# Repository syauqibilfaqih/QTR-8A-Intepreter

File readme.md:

# QTR-8A Interpreter 

This is the repository of QTR-8A Interpreter circuit that supports both digital data transmission through gpio pins and UART communication between master microcontroller and slave microcontroller, which is Arduino Nano, to read the QTR-8A sensor data. Use KiCad to open the schematic and board file, whereas use PlatformIO VS Code to open the code and build it.

To calibrate the line sensor, there are three ways to trigger the calibration mode:

1. By pressing button
2. By sending command "clib" via UART
3. By giving active signal to pin 12

Once the calibration mode is activated, move the sensors to get the black and white surface of the track. When it's done, the led indicators will show the correct reading state, where if the sensor read the black surface, the led will be turned on, otherwise it will be turned off.

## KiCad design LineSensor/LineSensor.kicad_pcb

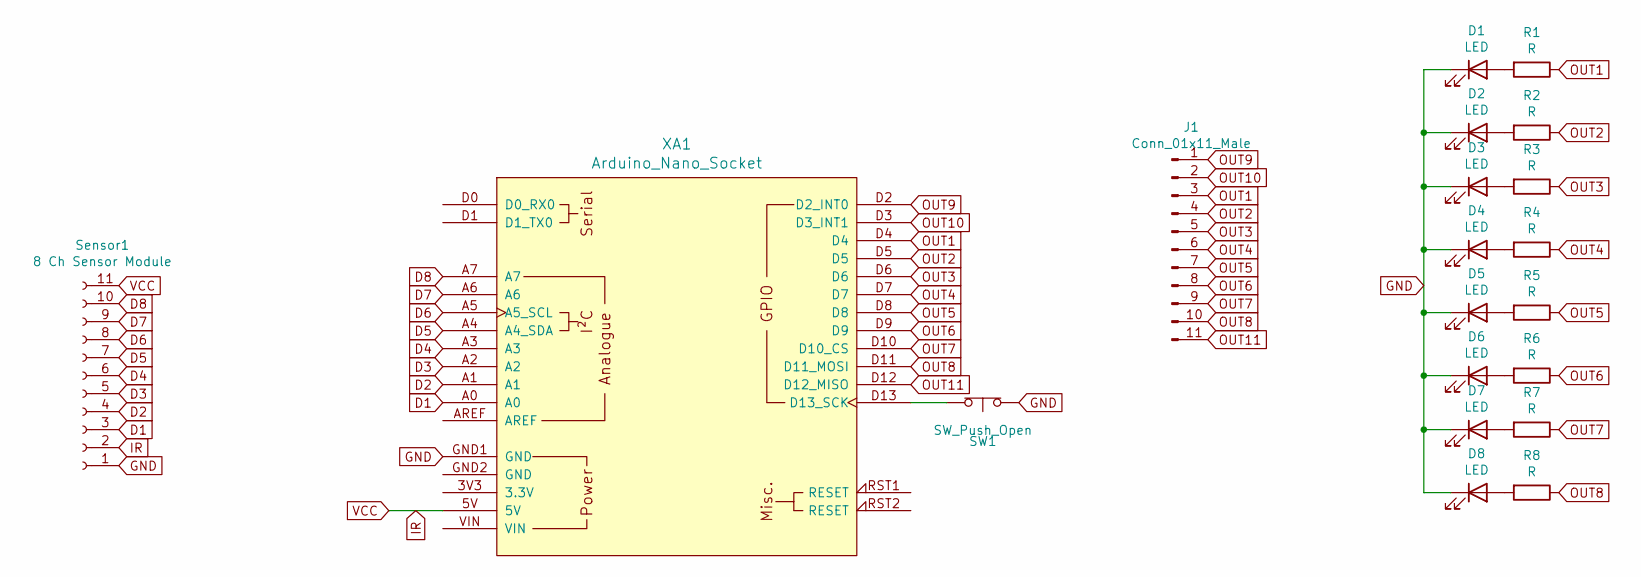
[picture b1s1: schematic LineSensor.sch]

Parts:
D1, D2, D3, D4, D5, D6, D7, D8: LED; LED_D3.0mm
J1: Conn_01x11_Male; PinHeader_1x11_P2.54mm_Vertical
R1, R2, R3, R4, R5, R6, R7, R8: R; R_Axial_DIN0207_L6.3mm_D2.5mm_P10.16mm_Horizontal
SW1: SW_Push_Open; SW_PUSH_6mm
Sensor1: 8 Ch Sensor Module; PinSocket_1x11_P2.54mm_Vertical
XA1: Arduino_Nano_Socket

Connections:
D1: Sensor1.3, XA1.A0
D2: Sensor1.4, XA1.A1
D3: Sensor1.5, XA1.A2
D4: Sensor1.6, XA1.A3
D5: Sensor1.7, XA1.A4 (A4_SDA)
D6: Sensor1.8, XA1.A5 (A5_SCL)
D7: Sensor1.9, XA1.A6
D8: Sensor1.10, XA1.A7
GND: D1.1 (K), D2.1 (K), D3.1 (K), D4.1 (K), D5.1 (K), D6.1 (K), D7.1 (K), D8.1 (K), SW1.1 (A), Sensor1.1, XA1.GND1 (GND)
IR: Sensor1.2, Sensor1.11, XA1.5V
unnamed: D1.2 (A), R1.2
unnamed: D2.2 (A), R2.2
unnamed: D3.2 (A), R3.2
unnamed: D4.2 (A), R4.2
unnamed: D5.2 (A), R5.2
unnamed: D6.2 (A), R6.2
unnamed: D7.2 (A), R7.2
unnamed: D8.2 (A), R8.2
unnamed: SW1.2 (B), XA1.D13 (D13_SCK)
OUT1: J1.3, R1.1, XA1.D4
OUT2: J1.4, R2.1, XA1.D5
OUT3: J1.5, R3.1, XA1.D6
OUT4: J1.6, R4.1, XA1.D7
OUT5: J1.7, R5.1, XA1.D8
OUT6: J1.8, R6.1, XA1.D9
OUT7: J1.9, R7.1, XA1.D10 (D10_CS)
OUT8: J1.10, R8.1, XA1.D11 (D11_MOSI)
OUT9: J1.1, XA1.D2 (D2_INT0)
OUT10: J1.2, XA1.D3 (D3_INT1)
OUT11: J1.11, XA1.D12 (D12_MISO)

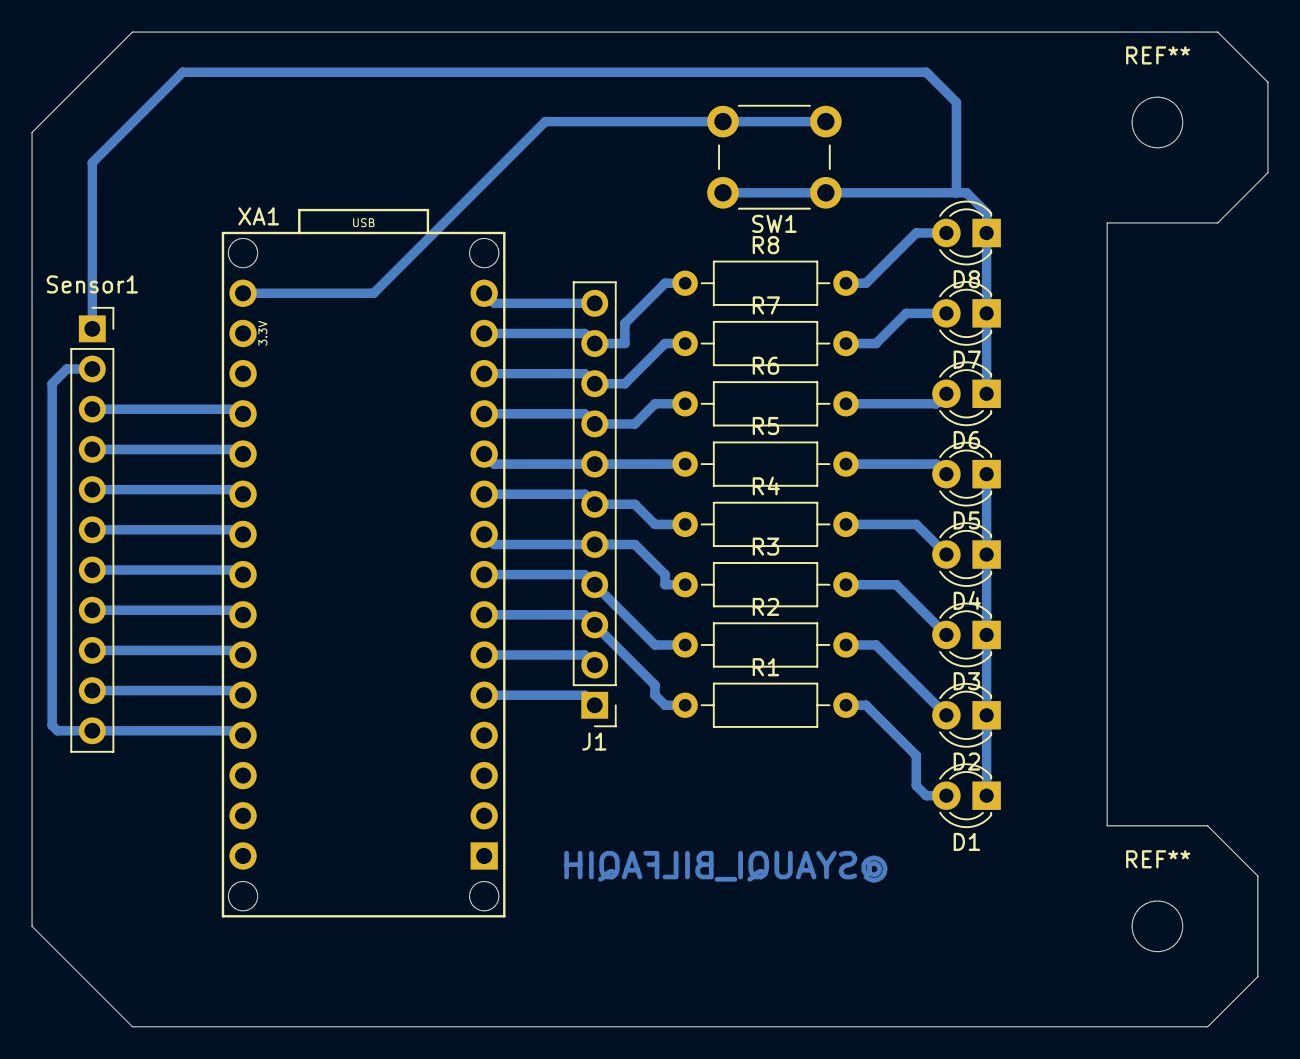
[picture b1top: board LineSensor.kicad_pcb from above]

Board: 2 copper layers, 78.1 x 62.9 mm, 20 parts (0 on the bottom side), 30 nets.
